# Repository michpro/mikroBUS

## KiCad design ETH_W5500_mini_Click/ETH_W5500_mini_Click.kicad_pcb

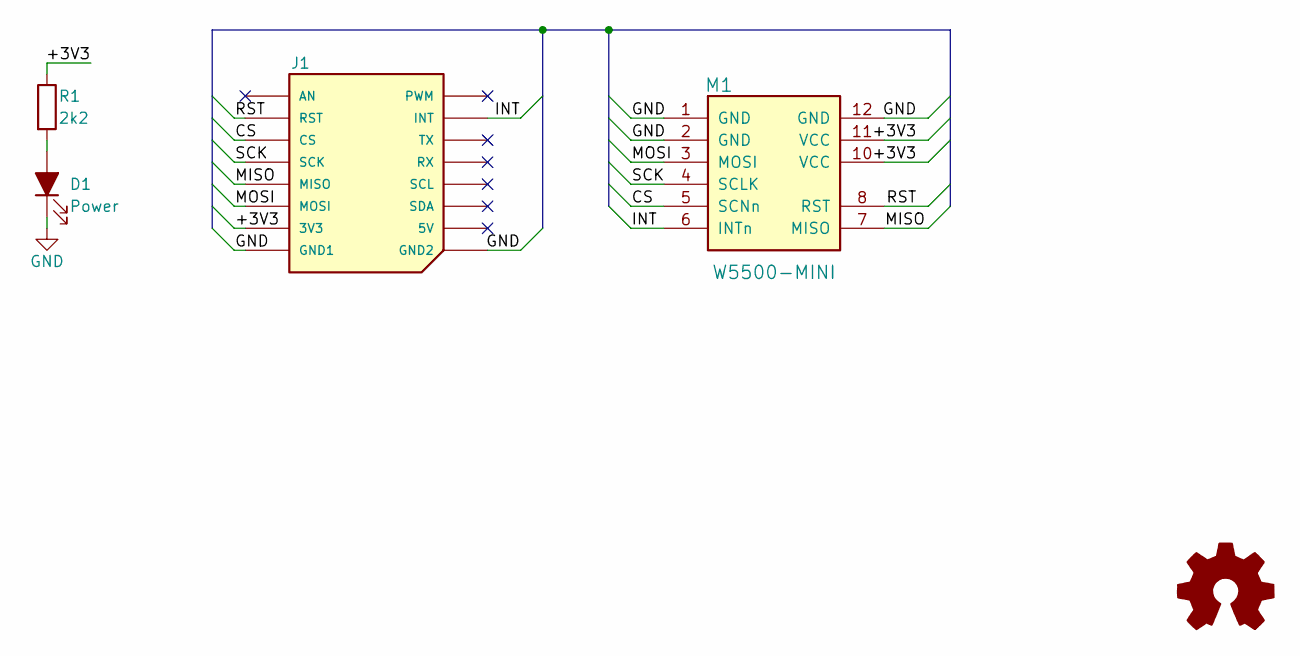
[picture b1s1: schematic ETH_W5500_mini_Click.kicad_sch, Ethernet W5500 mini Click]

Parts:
D1: Power; LED_0805_2012Metric; LCSC C2296
J1: ETH W5500 mini Click v1.0; mikroBUS_module_M
LOGO1: Logo_Open_Hardware_Small; OSHW-Logo2_7.3x6mm_SilkScreen
M1: W5500-MINI; LCSC n/a
R1: 2k2; R_0805_2012Metric; LCSC C17520

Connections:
/+3V3: J1.P7 (3V3), M1.10 (VCC), M1.11 (VCC), R1.1
/CS: J1.P3 (CS), M1.5 (SCNn)
/INT: J1.P15 (INT), M1.6 (INTn)
/MISO: J1.P5 (MISO), M1.7 (MISO)
/MOSI: J1.P6 (MOSI), M1.3 (MOSI)
/RST: J1.P2 (RST), M1.8 (RST)
/SCK: J1.P4 (SCK), M1.4 (SCLK)
GND: D1.1 (K), J1.P8 (GND1), J1.P9 (GND2), M1.1 (GND), M1.2 (GND), M1.12 (GND)
unnamed: D1.2 (A), R1.2

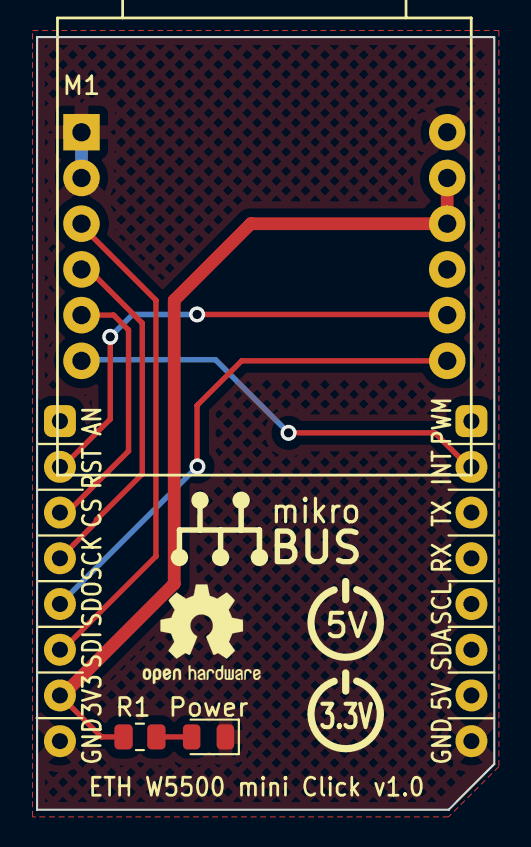
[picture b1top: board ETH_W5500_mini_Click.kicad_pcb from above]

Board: 2 copper layers, 25.4 x 42.9 mm, 5 parts (0 on the bottom side), 9 nets.

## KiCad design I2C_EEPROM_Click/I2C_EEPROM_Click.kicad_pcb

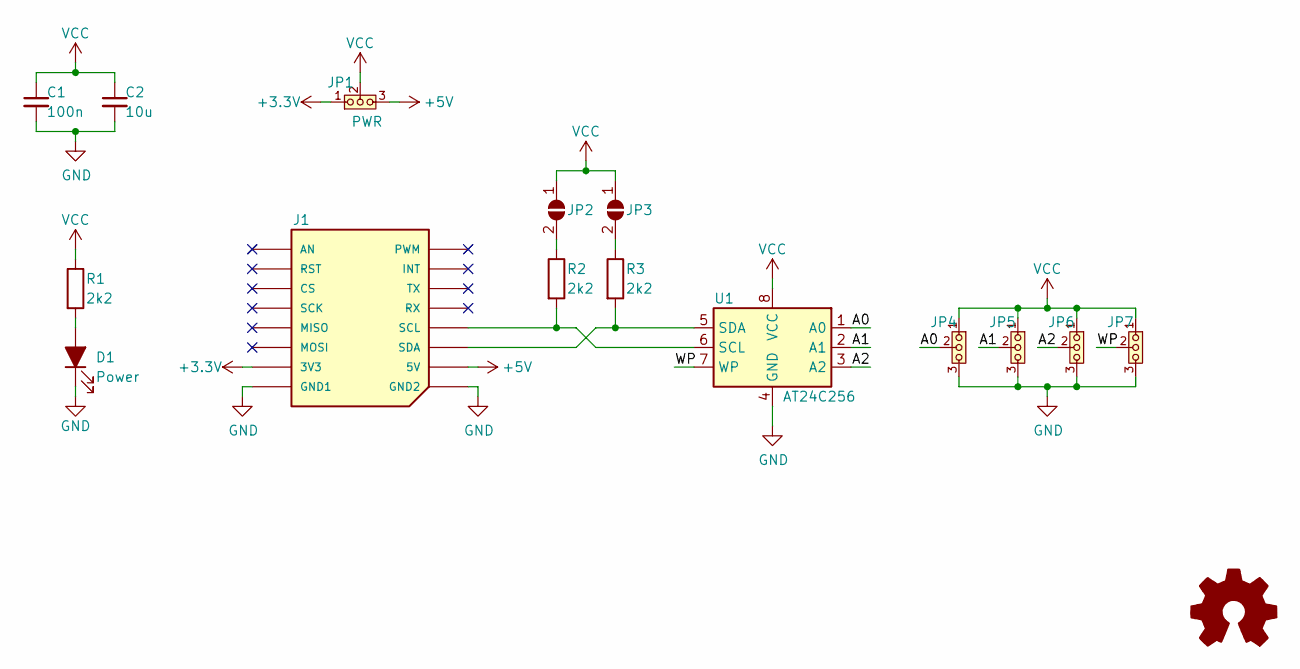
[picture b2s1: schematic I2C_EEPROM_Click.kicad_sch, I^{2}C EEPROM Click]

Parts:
C1: 100n; C_0805_2012Metric; LCSC C49678
C2: 10u; C_0805_2012Metric; LCSC C15850
D1: Power; LED_0805_2012Metric; LCSC C2296
J1: I^{2}C EEPROM Click v1.0 by MPro; mikroBUS_module_S; LCSC -----
JP1: PWR; PinHeader_1x03_P2.54mm_Vertical; LCSC -----
JP2: SCL; SolderJumper-2_P1.3mm_Open_TrianglePad1.0x1.5mm; LCSC -----
JP3: SDA; SolderJumper-2_P1.3mm_Open_TrianglePad1.0x1.5mm; LCSC -----
JP4: A0; PinHeader_1x03_P2.54mm_Vertical; LCSC -----
JP5: A1; PinHeader_1x03_P2.54mm_Vertical; LCSC -----
JP6: A2; PinHeader_1x03_P2.54mm_Vertical; LCSC -----
JP7: WP; PinHeader_1x03_P2.54mm_Vertical; LCSC -----
LOGO1: Logo_Open_Hardware_Small; OSHW-Logo2_7.3x6mm_SilkScreen
R1, R2, R3: 2k2; R_0805_2012Metric; LCSC C17520
U1: AT24C256; SO-8_3.9x4.9mm_P1.27mm; LCSC C90485

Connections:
+3.3V: J1.P7 (3V3), JP1.1 (A)
+5V: J1.P10 (5V), JP1.3 (B)
/A0: JP4.2 (C), U1.1 (A0)
/A1: JP5.2 (C), U1.2 (A1)
/A2: JP6.2 (C), U1.3 (A2)
/WP: JP7.2 (C), U1.7 (WP)
GND: C1.2, C2.2, D1.1 (K), J1.P8 (GND1), J1.P9 (GND2), JP4.3 (B), JP5.3 (B), JP6.3 (B), JP7.3 (B), U1.4 (GND)
unnamed: D1.2 (A), R1.2
unnamed: J1.P12 (SCL), R2.2, U1.6 (SCL)
unnamed: J1.P11 (SDA), R3.2, U1.5 (SDA)
unnamed: JP2.2 (B), R2.1
unnamed: JP3.2 (B), R3.1
VCC: C1.1, C2.1, JP1.2 (C), JP2.1 (A), JP3.1 (A), JP4.1 (A), JP5.1 (A), JP6.1 (A), JP7.1 (A), R1.1, U1.8 (VCC)

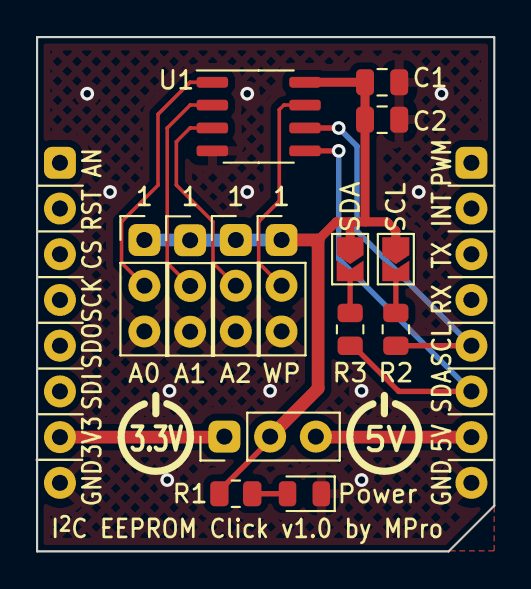
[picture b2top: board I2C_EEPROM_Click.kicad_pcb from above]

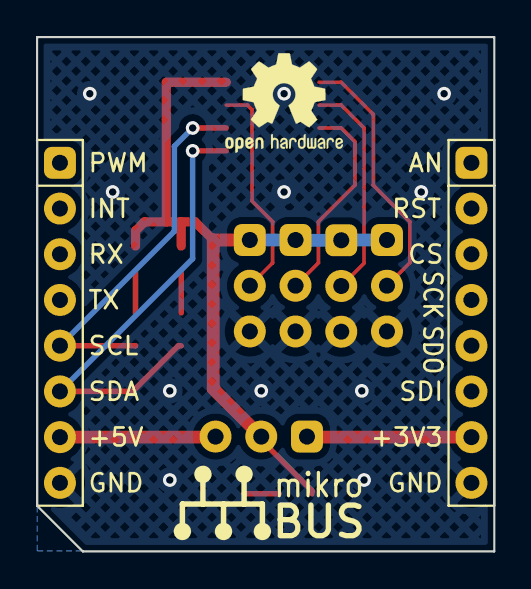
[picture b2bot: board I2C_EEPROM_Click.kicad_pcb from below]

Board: 2 copper layers, 25.4 x 28.6 mm, 19 parts (2 on the bottom side), 13 nets.

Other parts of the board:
REF1: LOGO; Logo_Power_3V3
REF2: LOGO; Logo_Power_5V
REF4: mikroBUS_logo_text

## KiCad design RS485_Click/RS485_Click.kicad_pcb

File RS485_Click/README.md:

# **RS485 Click**

- [**RS485 Click**](#rs485-click)
  - [**Overview**](#overview)
    - [**Features**](#features)
  - [**Schematic diagram**](#schematic-diagram)
  - [**Module visualisation**](#module-visualisation)
  - [**Assembly**](#assembly)
  - [**Production files**](#production-files)
  - [**Usage Instructions**](#usage-instructions)
    - [**1. Power Supply Selection**:](#1-power-supply-selection)
    - [**2. Jumper Configurations**:](#2-jumper-configurations)
    - [**3. Microcontroller Connection**:](#3-microcontroller-connection)
    - [**4. Software Configuration**:](#4-software-configuration)
    - [**5. LED Indicator**:](#5-led-indicator)
  - [**Reporting bugs**](#reporting-bugs)
  - [**License**](#license)
  - [**Support**](#support)

---

## **Overview**
The RS485 Click is a compact add-on board designed for RS485 communication, enabling reliable serial data transmission over long distances. It features the YD3082EESA RS485 transceiver chip and is compatible with the MikroBUS™ click board standard, making it suitable for integration with various microcontroller-based systems.

### **Features**
* RS485 communication interface via the YD3082EESA transceiver
* Supports +3.3V and +5V power supplies, selectable via jumper
* Jumper-configurable control signals for operational flexibility
* TVS diodes for protection against voltage spikes on the RS485 bus
* LED power indicator
* Compact design adhering to the click board standard

---

## **Schematic diagram**

## **Module visualisation**
(click on the image to see the 3D model)
<p align="center"></p>

## **Assembly**
[Interactive BOM and placement](https://michpro.github.io/mikroBUS/RS485_Click/docs/ibom.html)

## **Production files**
Production files can be found [**here**](./production/).

---

## **Usage Instructions**
### **1. Power Supply Selection**:
* Configure jumper JP4:
  * Pins 1-2: +3.3V operation
  * Pins 2-3: +5V operation
### **2. Jumper Configurations**:
* JP1 (Bias+): Close to enable pull-up on A line.
* JP2 (Bias-): Close to enable pull-down on B line.
* JP3 (Term): Close to enable 120Ω termination.
* JP5 (REN select): Set to configure Receiver Enable source.
### **3. Microcontroller Connection**:
* Connect via the click board interface, mapping RO, DI, DE, and RE to the microcontroller’s UART and I/O pins.
### **4. Software Configuration**:
* Implement RS485 half-duplex communication, managing DE and RE signals:
  * DE high to transmit, low to receive.
  * RE can mirror DE or be controlled separately (JP5).
### **5. LED Indicator**:
* D4 illuminates when the board is powered.

---

## **Reporting bugs**

[Create an issue on GitHub](https://github.com/michpro/mikroBUS/issues)

---

## **License**
Copyright © 2023-2025 Michal Protasowicki

This project is released under CERN Open Hardware Licence Version 2 - Permissive.

---

## **Support**
If You find my projects interesting and You wanted to support my work, You can give me a cup of coffee or a keg of beer :)

&nbsp;&nbsp;&nbsp;&nbsp;&nbsp;&nbsp;&nbsp;&nbsp;&nbsp;&nbsp;

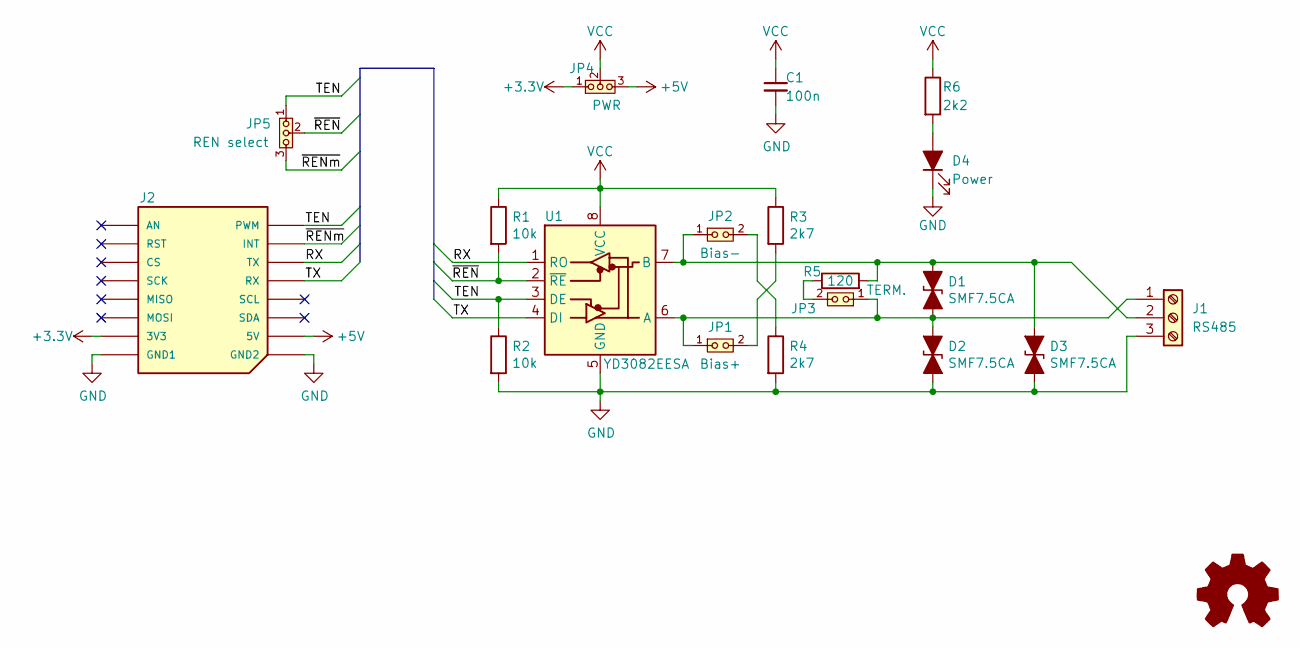
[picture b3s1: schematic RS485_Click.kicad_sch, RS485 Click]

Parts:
C1: 100n; C_0805_2012Metric; LCSC C49678
D1, D2, D3: SMF7.5CA; D_SOD-123; LCSC C123797
D4: Power; LED_0805_2012Metric; LCSC C2296
J1: RS485; TerminalBlock_MetzConnect_Type086_RT03403HBLC_1x03_P3.81mm_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; LCSC -----
J2: RS485 Click v1.0 by MPro; mikroBUS_module_M; LCSC -----
JP1: Bias+; PinHeader_1x02_P2.54mm_Vertical; LCSC -----
JP2: Bias-; PinHeader_1x02_P2.54mm_Vertical; LCSC -----
JP3: TERM.; PinHeader_1x02_P2.54mm_Vertical; LCSC -----
JP4: PWR; PinHeader_1x03_P2.54mm_Vertical; LCSC -----
JP5: REN select; PinHeader_1x03_P2.54mm_Vertical; LCSC -----
LOGO1: Logo_Open_Hardware_Small; OSHW-Logo2_7.3x6mm_SilkScreen
R1, R2: 10k; R_0805_2012Metric; LCSC C17414
R3, R4: 2k7; R_0805_2012Metric; LCSC C17530
R5: 120; R_0805_2012Metric; LCSC C17437
R6: 2k2; R_0805_2012Metric; LCSC C17520
U1: YD3082EESA; SO-8_3.9x4.9mm_P1.27mm; LCSC C269866

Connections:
+3.3V: J2.P7 (3V3), JP4.1 (A)
+5V: J2.P10 (5V), JP4.3 (B)
/RX: J2.P14 (TX), U1.1 (RO)
/TEN: J2.P16 (PWM), JP5.1 (A), R2.1, U1.3 (DE)
/TX: J2.P13 (RX), U1.4 (DI)
/~RENm: J2.P15 (INT), JP5.3 (B)
/~REN: JP5.2 (C), R1.2, U1.2 (~RE)
GND: C1.2, D2.2 (A2), D3.2 (A2), D4.1 (K), J1.3, J2.P8 (GND1), J2.P9 (GND2), R2.2, R4.2, U1.5 (GND)
unnamed: D1.1 (A1), D3.1 (A1), J1.2, JP2.1 (A), R5.2, U1.7 (B)
unnamed: D1.2 (A2), D2.1 (A1), J1.1, JP1.1 (A), JP3.1 (A), U1.6 (A)
unnamed: D4.2 (A), R6.2
unnamed: JP1.2 (B), R3.2
unnamed: JP2.2 (B), R4.1
unnamed: JP3.2 (B), R5.1
VCC: C1.1, JP4.2 (C), R1.1, R3.1, R6.1, U1.8 (VCC)

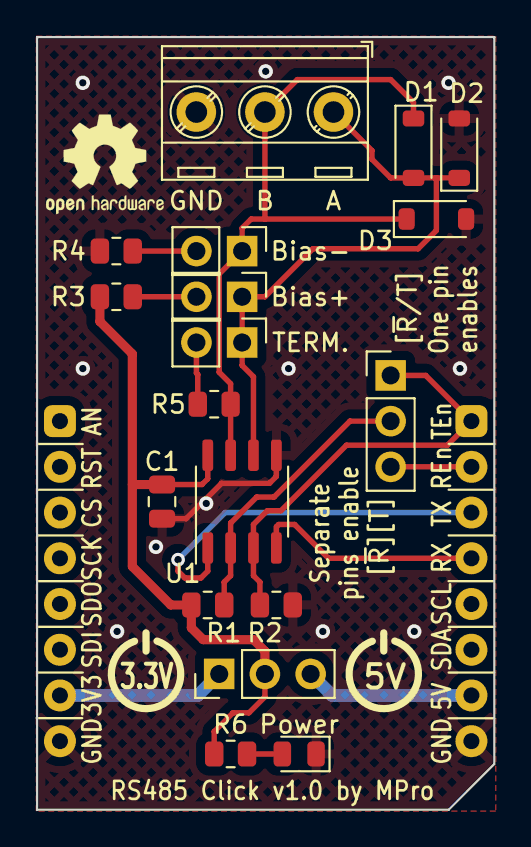
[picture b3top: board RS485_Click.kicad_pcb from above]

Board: 2 copper layers, 25.4 x 42.9 mm, 22 parts (0 on the bottom side), 15 nets.

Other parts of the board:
REF1: LOGO; Logo_Power_5V
REF2: LOGO; Logo_Power_3V3

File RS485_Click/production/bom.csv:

Designator,Footprint,Quantity,Value,LCSC Part #
C1,0805,1,100n,C49678
"D1, D2, D3",D_SOD-123,3,SMF7.5CA,C123797
D4,0805,1,Power,C2296
J1,TerminalBlock_MetzConnect_Type086_RT03403HBLC_1x03_P3.81mm_Horizontal,1,RS485,-----
JP1,PinHeader_1x02_P2.54mm_Vertical,1,Bias+,-----
JP2,PinHeader_1x02_P2.54mm_Vertical,1,Bias-,-----
JP3,PinHeader_1x02_P2.54mm_Vertical,1,TERM.,-----
JP4,PinHeader_1x03_P2.54mm_Vertical,1,PWR,-----
JP5,PinHeader_1x03_P2.54mm_Vertical,1,REN select,-----
"R1, R2",0805,2,10k,C17414
"R3, R4",0805,2,2k7,C17530
R5,0805,1,120,C17437
R6,0805,1,2k2,C17520
U1,SO-8_3.9x4.9mm_P1.27mm,1,YD3082EESA,C269866

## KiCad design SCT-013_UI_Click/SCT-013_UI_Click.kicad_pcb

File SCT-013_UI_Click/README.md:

# **UI Click with SCT-013 interface**

- [**UI Click with SCT-013 interface**](#ui-click-with-sct-013-interface)
  - [**Overview**](#overview)
    - [**Features**](#features)
  - [**SCT-013 interface**](#sct-013-interface)
      - [**Note**](#note)
      - [**Visual simulation**](#visual-simulation)
  - [**Schematic diagram**](#schematic-diagram)
  - [**Module visualisation**](#module-visualisation)
  - [**Assembly**](#assembly)
  - [**Production files**](#production-files)
  - [**Reporting bugs**](#reporting-bugs)
  - [**License**](#license)
  - [**Support**](#support)

---

## **Overview**
The UI Click with SCT-013 interface is an open-hardware project designed to interface with the SCT-013 non-invasive current transformer sensor. It incorporates a user interface featuring a 0.96-inch I²C OLED display and a rotary encoder with an integrated switch for user interaction. This project supports both 3.3V and 5V power rails and includes an LED for power indication.

### **Features**
* **Sensor Interface**: Connects to the SCT-013 current transformer via a 3-pole audio jack.
* **Display**: Utilizes a 0.96-inch I2C OLED display for visual feedback.
* **User Input**: Features a rotary encoder with a push switch for navigation and control.
* **Power Supply**: Operates on 3.3V and 5V power rails.
* **Indicator**: Includes a yellow LED for power indication.

---

## **SCT-013 interface**
The circuit is designed for transducers with a voltage output of 1V. The signal from SCT-013 with an effective amplitude ranging from -1.42V to +1.42V is processed in the R8, R9, R10, R11 circuit into a useful signal ranging from 0 to 1V, which is then converted by the microcontroller ADC converter into digital form.
#### **Note**
* If an output voltage in the range of 0 to 3.3V is required, resistor R10 must be replaced with a 0Ω jumper and resistor R11 must be removed from the PCB.
#### [**Visual simulation**](https://falstad.com/circuit/circuitjs.html?ctz=CQAgjCAMB0l3BWcMBMcUHYMGZIA4UA2ATmIxAUgpABZsKBTAWjDACgAncMFEFFGt17FCUZPDYB3ISBG08s0ZDYBjcISrYEvMBr4DaUWPEikz5i6RAtohAQmLZiBQhhpgavKsoBu8kFq8NApy3rSa0PRhMAicMoEy-IJUYCZSiQa6VElQ6cEB2vGFytKsvAlZBV5sAOb+CfnYhArebH6VOSgIojkpFCnQnmLe0LFcXT14ChP6yfpp491VfEsoU2KpaaV6CTMJygAO1rqKx6IJURsmEkfYaHzrd5qFlynXcOkzawpPDy2fSwu9326RYojk+VCoJODR+xTYRzovG+tDuy1e4muAJ6BiRs1y0jxOSJ6xKqPKL2B8IA9nwUkpwPxiBBsLA6IQaMEwI5NsQvMZIBAqIJgeAkCkkNg2NhpiAAGJCozXIUC1IQFggADCAEMDtqVABLAAu2oAdioGNKWvLFRA1ccQAAlBgAZwNLpN5stQA)

---

## **Schematic diagram**

## **Module visualisation**
(click on the image to see the 3D model)
<p align="center"></p>

## **Assembly**
[Interactive BOM and placement](https://michpro.github.io/mikroBUS/SCT-013_UI_Click/docs/ibom.html)

## **Production files**
Production files can be found [**here**](./production/).

---

## **Reporting bugs**

[Create an issue on GitHub](https://github.com/michpro/mikroBUS/issues)

---

## **License**
Copyright © 2025 Michal Protasowicki

This project is released under CERN Open Hardware Licence Version 2 - Permissive.

---

## **Support**
If You find my projects interesting and You wanted to support my work, You can give me a cup of coffee or a keg of beer :)

&nbsp;&nbsp;&nbsp;&nbsp;&nbsp;&nbsp;&nbsp;&nbsp;&nbsp;&nbsp;

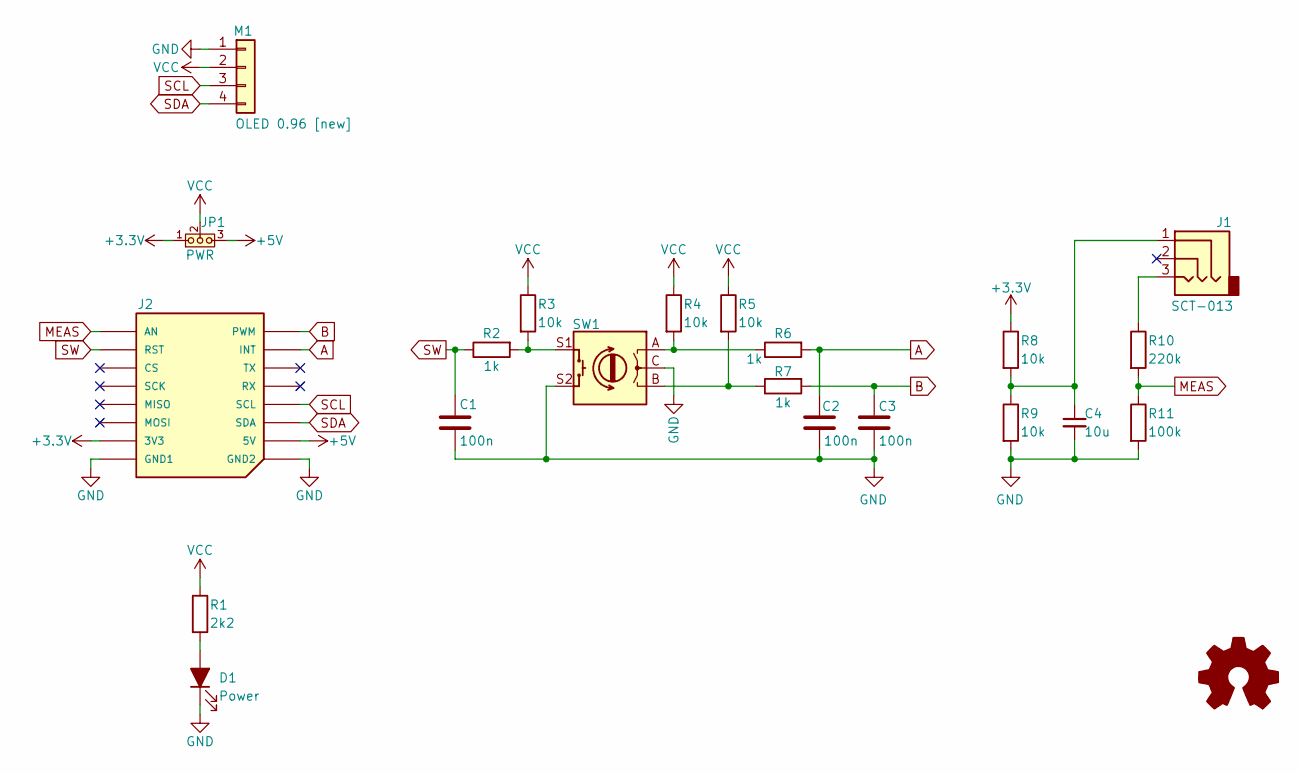
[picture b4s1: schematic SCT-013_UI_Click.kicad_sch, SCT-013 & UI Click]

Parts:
C1, C2, C3: 100n; C_0805_2012Metric; LCSC C49678
C4: 10u; C_0805_2012Metric; LCSC C15850
D1: Power; LED_0805_2012Metric; LCSC C2296
J1: SCT-013; PJ-320B; LCSC C2884998
J2: SCT-013 & UI Click v${REVISION} by MPro; mikroBUS_module_L; LCSC -----
JP1: PWR; PinHeader_1x03_P2.54mm_Vertical; LCSC -----
LOGO1: Logo_Open_Hardware_Small; OSHW-Logo2_7.3x6mm_SilkScreen
M1: OLED 0.96 [new]; 128X64_OLED_I2C_0-96inch (EstarDyn); LCSC ------
R1: 2k2; R_0805_2012Metric; LCSC C17520
R2, R6, R7: 1k; R_0805_2012Metric; LCSC C17513
R3, R4, R5, R8, R9: 10k; R_0805_2012Metric; LCSC C17414
R10: 220k; R_0805_2012Metric; LCSC C17556
R11: 100k; R_0805_2012Metric; LCSC C149504
SW1: EC11 Encoder; EC11_SMD; LCSC -----

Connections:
+3.3V: J2.P7 (3V3), JP1.1 (A), R8.1
+5V: J2.P10 (5V), JP1.3 (B)
A: C2.2, J2.P15 (INT), R6.2
B: C3.2, J2.P16 (PWM), R7.2
GND: C1.1, C2.1, C3.1, C4.2, D1.1 (K), J2.P8 (GND1), J2.P9 (GND2), M1.1, R9.2, R11.2, SW1.C, SW1.S2
MEAS: J2.P1 (AN), R10.2, R11.1
unnamed: C4.1, J1.1, R8.2, R9.1
unnamed: D1.2 (A), R1.2
unnamed: J1.3, R10.1
unnamed: R2.2, R3.2, SW1.S1
unnamed: R4.2, R6.1, SW1.A
unnamed: R5.2, R7.1, SW1.B
SCL: J2.P12 (SCL), M1.3
SDA: J2.P11 (SDA), M1.4
SW: C1.2, J2.P2 (RST), R2.1
VCC: JP1.2 (C), M1.2, R1.1, R3.1, R4.1, R5.1

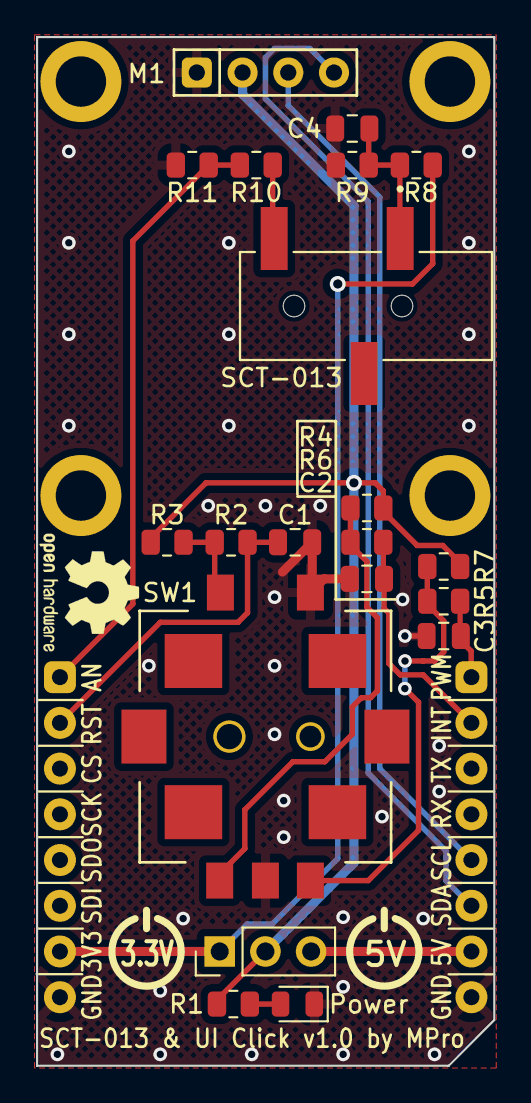
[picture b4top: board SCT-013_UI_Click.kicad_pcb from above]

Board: 2 copper layers, 25.4 x 57.1 mm, 22 parts (0 on the bottom side), 16 nets.

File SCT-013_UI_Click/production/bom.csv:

Designator,Footprint,Quantity,Value,LCSC Part #
"C1, C2, C3",0805,3,100n,C49678
C4,0805,1,10u,C15850
D1,0805,1,Power,C2296
J1,PJ-320B,1,SCT-013,C2884998
R1,0805,1,2k2,C17520
R10,0805,1,220k,C17556
R11,0805,1,100k,C149504
"R2, R6, R7",0805,3,1k,C17513
"R3, R4, R5, R8, R9",0805,5,10k,C17414

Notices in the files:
ETH_W5500_mini_Click/ETH_W5500_mini_Click.kicad_pcb:
© 2023 MPro
Licensed under CERN-OHL-P v2 or any later version
SCT-013_UI_Click/SCT-013_UI_Click.kicad_pcb:
© 2025 MPro
